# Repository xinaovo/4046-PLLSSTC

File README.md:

# 4046 PLLSSTC

## About this repository

This repository contains PCB designs and documents of the CD4046-based PLLSSTC project.

## PCB Designs

### Power Board

TODO

### 4046 PLL Board

TODO

### Mosfet Driver & GDT Board

TODO

### Full-Bridge Inverter Board

TODO

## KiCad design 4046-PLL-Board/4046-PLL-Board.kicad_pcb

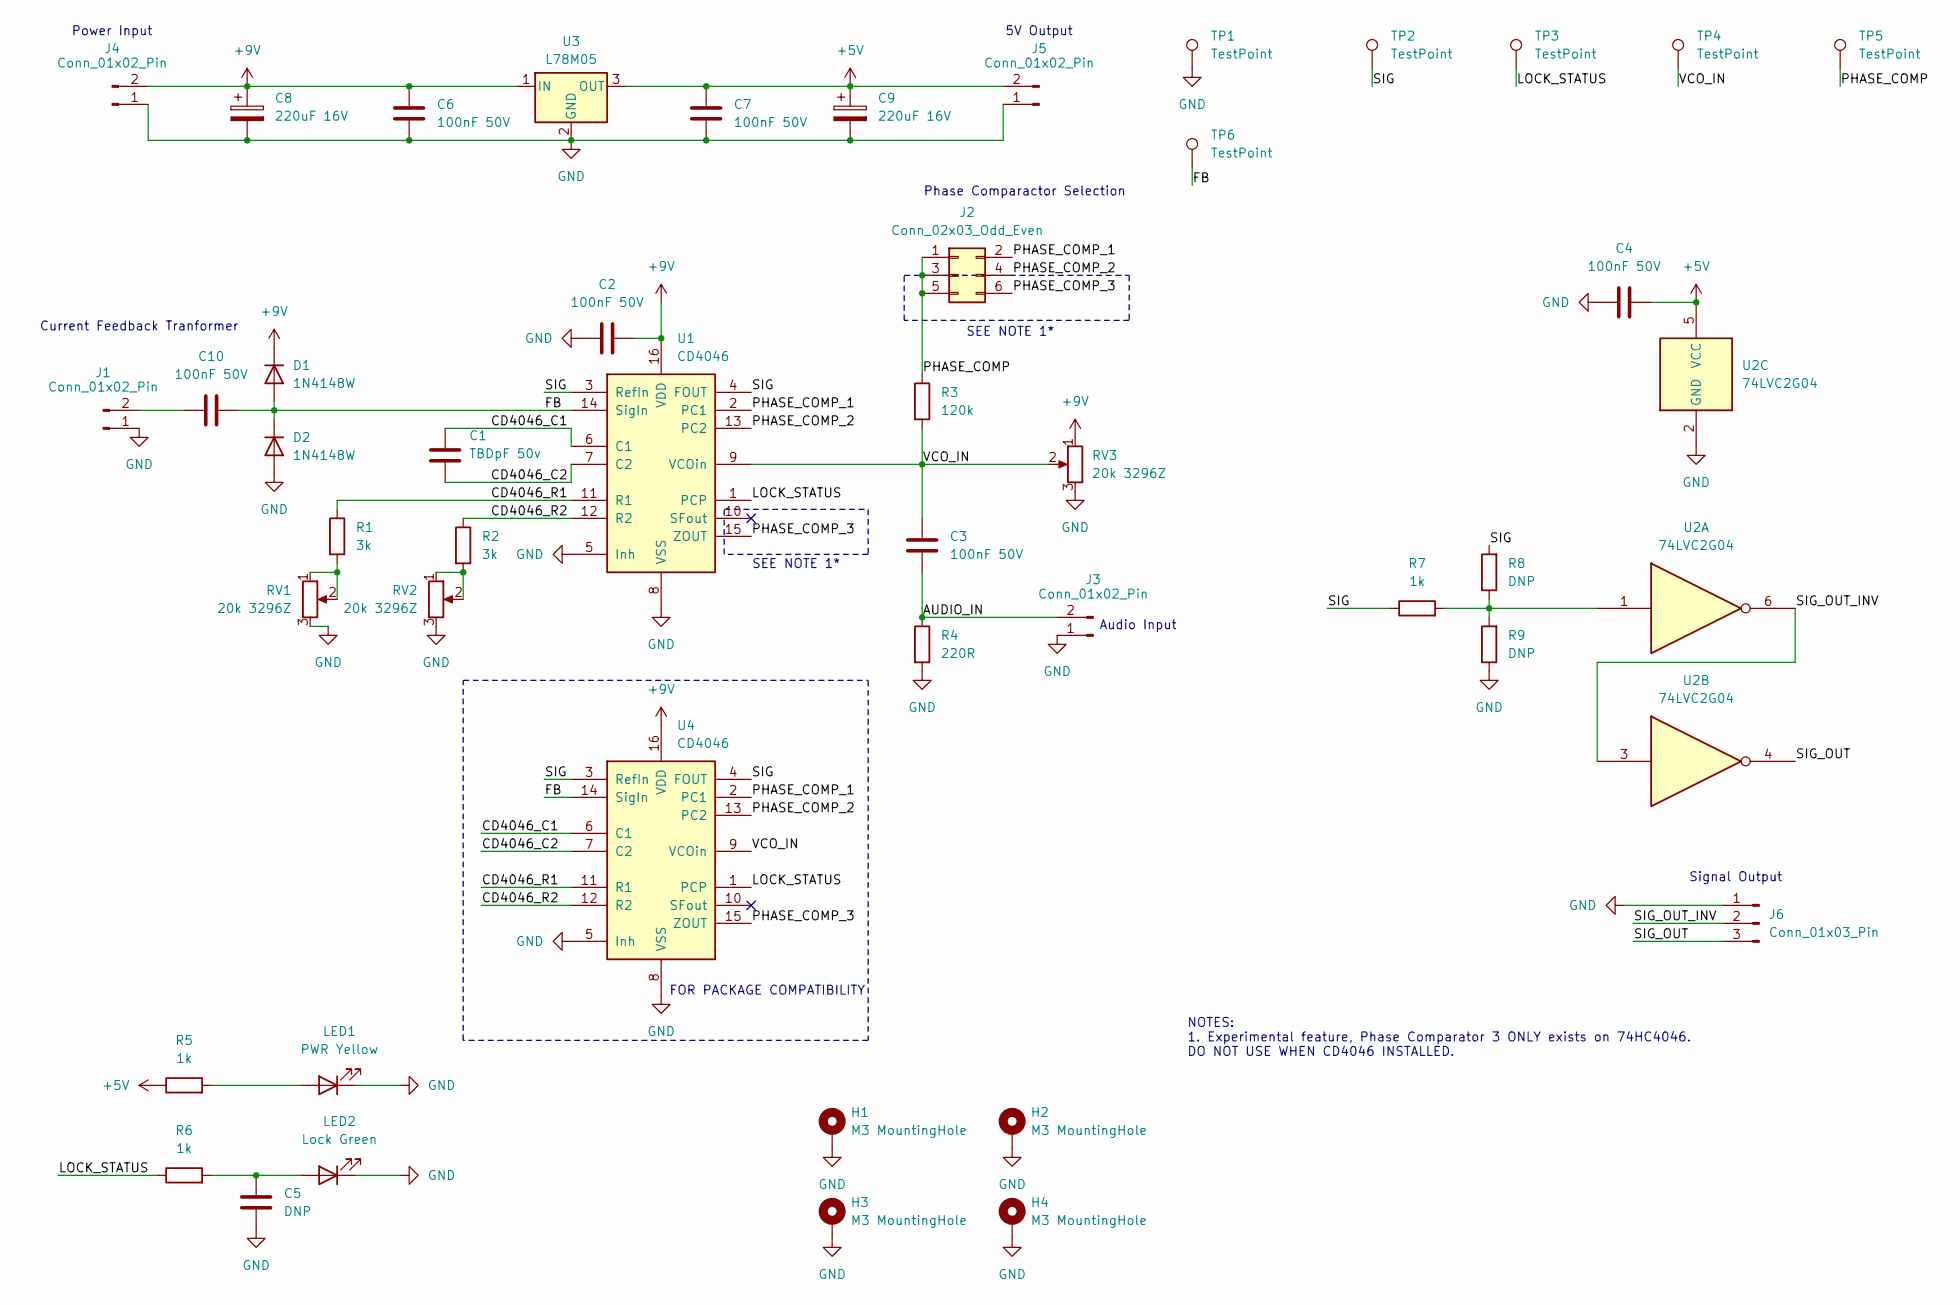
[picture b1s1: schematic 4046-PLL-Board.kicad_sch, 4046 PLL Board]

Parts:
C1: TBDpF 50v; C_Disc_D5.0mm_W2.5mm_P2.50mm
C2, C4, C6, C7: 100nF 50V; C_0603_1608Metric_Pad1.08x0.95mm_HandSolder
C3, C10: 100nF 50V; C_Disc_D5.0mm_W2.5mm_P2.50mm
C5: DNP; C_0603_1608Metric_Pad1.08x0.95mm_HandSolder
C8, C9: 220uF 16V; CP_Radial_D6.3mm_P2.50mm
D1, D2: 1N4148W; D_SOD-123
H1, H2, H3, H4: M3 MountingHole; MountingHole_3.2mm_M3_DIN965_Pad_TopBottom
J1, J3, J4, J5: Conn_01x02_Pin; JST_XH_B2B-XH-A_1x02_P2.50mm_Vertical
J2: Conn_02x03_Odd_Even; PinHeader_2x03_P2.54mm_Vertical
J6: Conn_01x03_Pin; JST_XH_B3B-XH-A_1x03_P2.50mm_Vertical
LED1: PWR Yellow; LED_0603_1608Metric_Pad1.05x0.95mm_HandSolder
LED2: Lock Green; LED_0603_1608Metric_Pad1.05x0.95mm_HandSolder
R1, R2: 3k; R_0603_1608Metric_Pad0.98x0.95mm_HandSolder
R3: 120k; R_Axial_DIN0207_L6.3mm_D2.5mm_P7.62mm_Horizontal
R4: 220R; R_Axial_DIN0207_L6.3mm_D2.5mm_P7.62mm_Horizontal
R5, R6, R7: 1k; R_0603_1608Metric_Pad0.98x0.95mm_HandSolder
R8, R9: DNP; R_0603_1608Metric_Pad0.98x0.95mm_HandSolder
RV1, RV2, RV3: 20k 3296Z; Potentiometer_Bourns_3296X_Horizontal
TP1, TP2, TP3, TP4, TP5, TP6: TestPoint; TestPoint_Loop_D2.50mm_Drill1.0mm
U1: CD4046; SOIC-16_4.55x10.3mm_P1.27mm
U2: 74LVC2G04; SOT-23-6_Handsoldering
U3: L78M05; TO-252-2
U4: CD4046; SOIC-16_3.9x9.9mm_P1.27mm

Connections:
+5V: C4.2, C7.2, C9.1, J5.2, R5.1, U2.5 (VCC), U3.3 (OUT)
+9V: C2.2, C6.2, C8.1, D1.1 (K), J4.2, RV3.1, U1.16 (VDD), U3.1 (IN), U4.16 (VDD)
/AUDIO_IN: C3.1, J3.2, R4.1
/CD4046_C1: C1.1, U1.6 (C1), U4.6 (C1)
/CD4046_C2: C1.2, U1.7 (C2), U4.7 (C2)
/CD4046_R1: R1.1, U1.11 (R1), U4.11 (R1)
/CD4046_R2: R2.1, U1.12 (R2), U4.12 (R2)
/FB: C10.1, D1.2 (A), D2.1 (K), TP6.1, U1.14 (SigIn), U4.14 (SigIn)
/LOCK_STATUS: R6.1, TP3.1, U1.1 (PCP), U4.1 (PCP)
/PHASE_COMP: J2.1, J2.3, J2.5, R3.1, TP5.1
/PHASE_COMP_1: J2.2, U1.2 (PC1), U4.2 (PC1)
/PHASE_COMP_2: J2.4, U1.13 (PC2), U4.13 (PC2)
/PHASE_COMP_3: J2.6, U1.15 (ZOUT), U4.15 (ZOUT)
/SIG: R7.1, R8.2, TP2.1, U1.3 (RefIn), U1.4 (FOUT), U4.3 (RefIn), U4.4 (FOUT)
/SIG_OUT: J6.3, U2.4
/SIG_OUT_INV: J6.2, U2.3, U2.6
/VCO_IN: C3.2, R3.2, RV3.2, TP4.1, U1.9 (VCOin), U4.9 (VCOin)
GND: C2.1, C4.1, C5.1, C6.1, C7.1, C8.2, C9.2, D2.2 (A), H1.1, H2.1, H3.1, H4.1, J1.1, J3.1, J4.1, J5.1, J6.1, LED1.1 (K), LED2.1 (K), R4.2, R9.1, RV1.3, RV2.3, RV3.3, TP1.1, U1.5 (Inh), U1.8 (VSS), U2.2 (GND), U3.2 (GND), U4.5 (Inh), U4.8 (VSS)
unnamed: C10.2, J1.2
unnamed: LED1.2 (A), R5.2
unnamed: C5.2, LED2.2 (A), R6.2
unnamed: R1.2, RV1.1, RV1.2
unnamed: R2.2, RV2.1, RV2.2
unnamed: R7.2, R8.1, R9.2, U2.1

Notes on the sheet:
Audio Input
SEE NOTE 1*
Signal Output
Current Feedback Tranformer
Power Input
Phase Comparactor Selection
5V Output
FOR PACKAGE COMPATIBILITY
NOTES: 1. Experimental feature, Phase Comparator 3 ONLY exists on 74HC4046. DO NOT USE WHEN CD4046 INSTALLED.

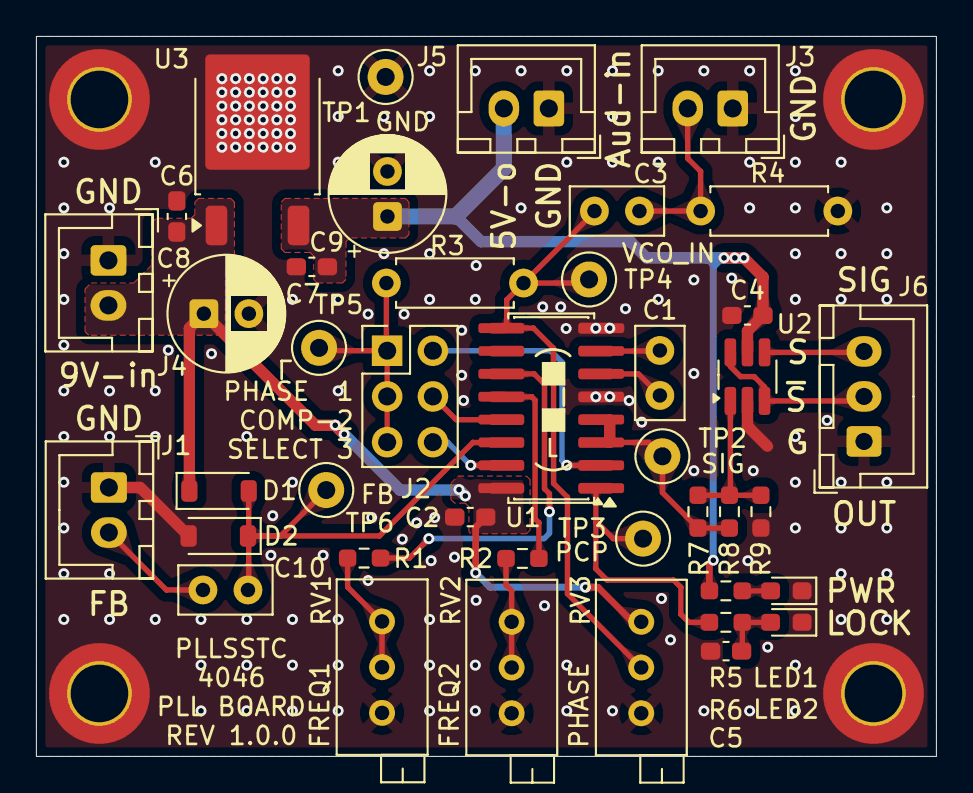
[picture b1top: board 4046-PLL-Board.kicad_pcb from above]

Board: 2 copper layers, 50.0 x 40.0 mm, 46 parts (0 on the bottom side), 24 nets.

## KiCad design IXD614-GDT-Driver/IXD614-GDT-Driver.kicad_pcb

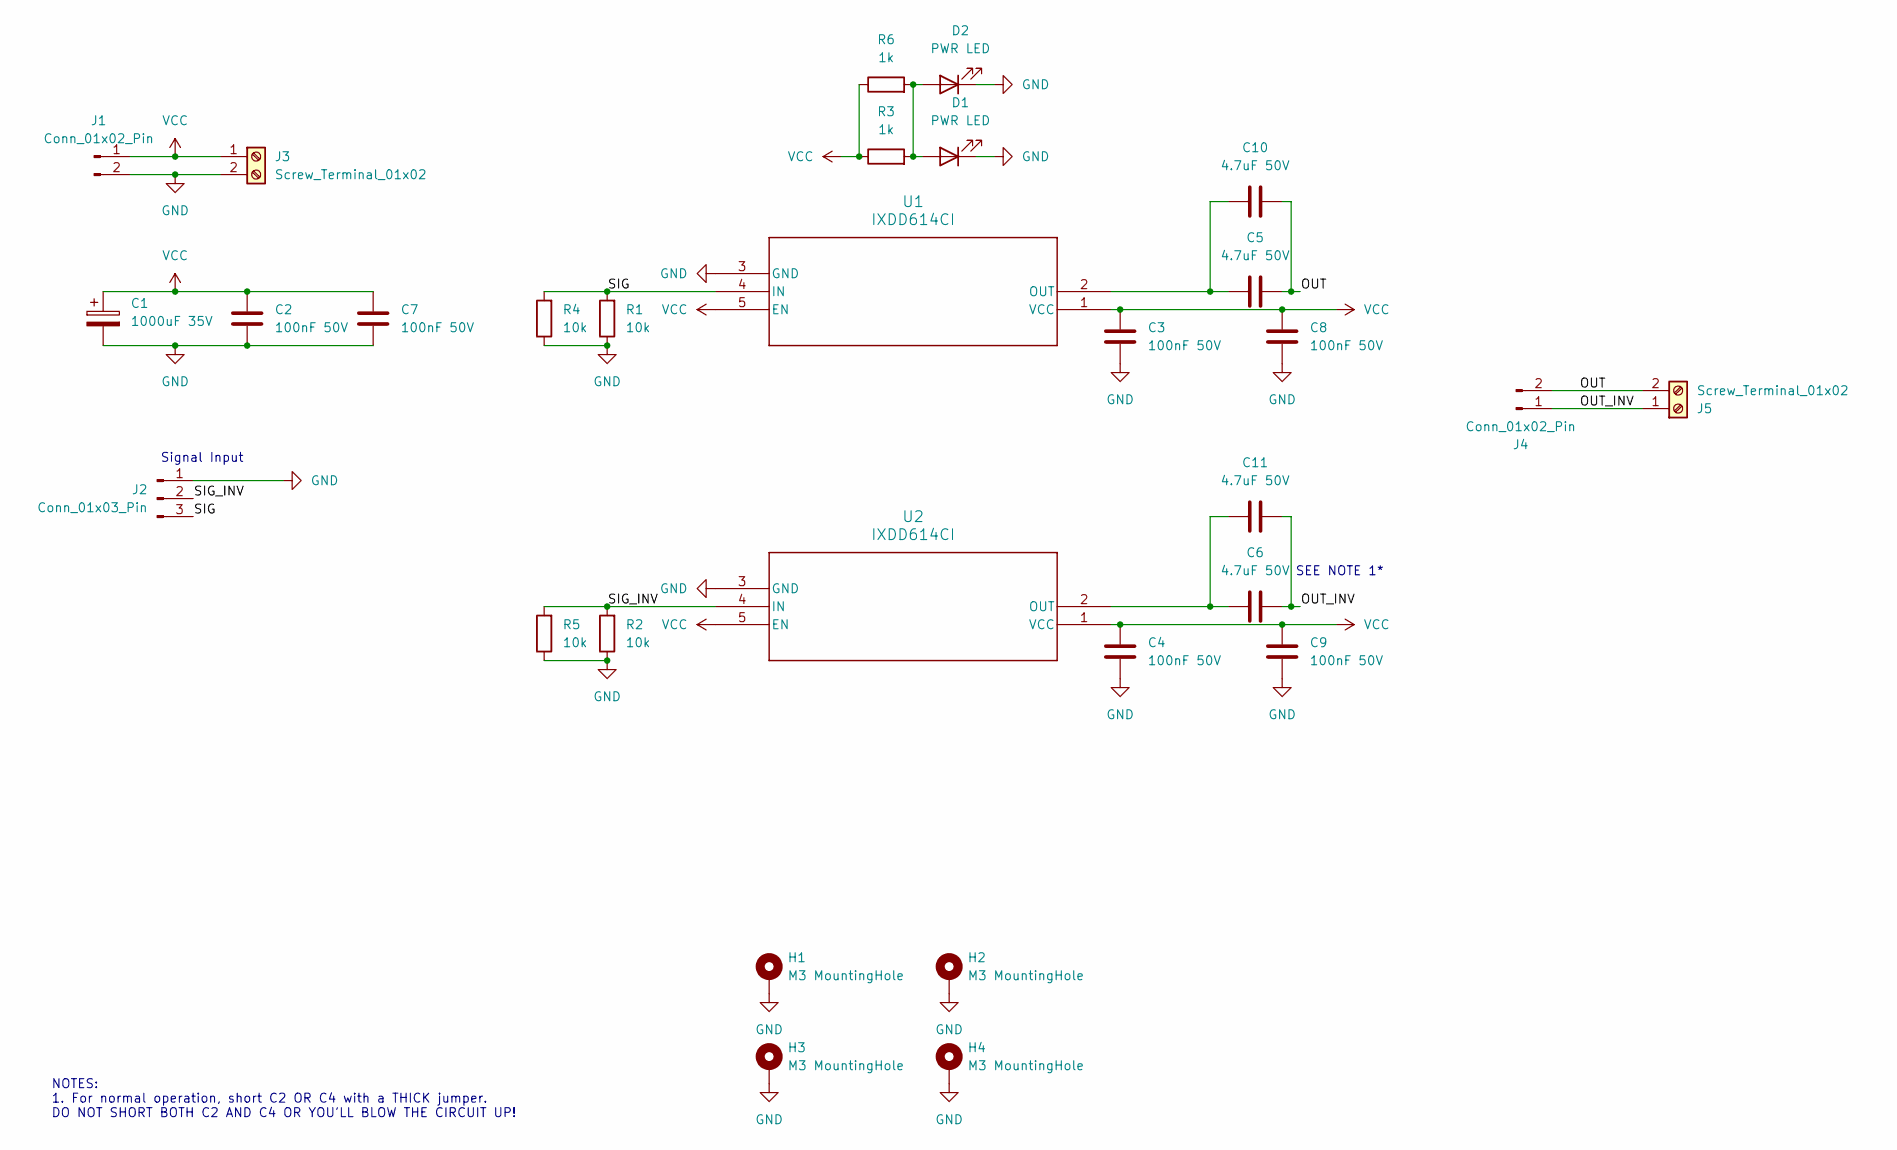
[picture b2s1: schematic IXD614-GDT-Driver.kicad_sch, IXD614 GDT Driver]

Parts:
C1: 1000uF 35V; CP_Radial_D10.0mm_P2.50mm_P5.00mm
C2, C3, C4: 100nF 50V; C_Disc_D5.0mm_W2.5mm_P5.00mm
C5, C6: 4.7uF 50V; C_Disc_D6.0mm_W4.4mm_P5.00mm
C7, C8, C9: 100nF 50V; C_0603_1608Metric_Pad1.08x0.95mm_HandSolder
C10, C11: 4.7uF 50V; C_1210_3225Metric
D1: PWR LED; LED_D5.0mm
D2: PWR LED; LED_0603_1608Metric_Pad1.05x0.95mm_HandSolder
H1, H2, H3, H4: M3 MountingHole; MountingHole_3.2mm_M3_DIN965_Pad_TopBottom
J1, J4: Conn_01x02_Pin; JST_XH_B2B-XH-A_1x02_P2.50mm_Vertical
J2: Conn_01x03_Pin; JST_XH_B3B-XH-A_1x03_P2.50mm_Vertical
J3, J5: Screw_Terminal_01x02; Wuerth_691311400102_P7.62mm
R1, R2: 10k; R_Axial_DIN0207_L6.3mm_D2.5mm_P7.62mm_Horizontal
R3: 1k; R_Axial_DIN0207_L6.3mm_D2.5mm_P7.62mm_Horizontal
R4, R5: 10k; R_0603_1608Metric_Pad0.98x0.95mm_HandSolder
R6: 1k; R_0603_1608Metric_Pad0.98x0.95mm_HandSolder
U1, U2: IXDD614CI; TO-220-5_Vertical

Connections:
/OUT: C5.2, C10.2, J4.2, J5.2
/OUT_INV: C6.2, C11.2, J4.1, J5.1
/SIG: J2.3, R1.2, R4.2, U1.4 (IN)
/SIG_INV: J2.2, R2.2, R5.2, U2.4 (IN)
GND: C1.2, C2.2, C3.2, C4.2, C7.2, C8.2, C9.2, D1.1 (K), D2.1 (K), H1.1, H2.1, H3.1, H4.1, J1.2, J2.1, J3.2, R1.1, R2.1, R4.1, R5.1, U1.3 (GND), U2.3 (GND)
unnamed: D1.2 (A), D2.2 (A), R3.2, R6.2
unnamed: C5.1, C10.1, U1.2 (OUT)
unnamed: C6.1, C11.1, U2.2 (OUT)
VCC: C1.1, C2.1, C3.1, C4.1, C7.1, C8.1, C9.1, J1.1, J3.1, R3.1, R6.1, U1.1 (VCC), U1.5 (EN), U2.1 (VCC), U2.5 (EN)

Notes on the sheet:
SEE NOTE 1*
Signal Input
NOTES: 1. For normal operation, short C2 OR C4 with a THICK jumper. DO NOT SHORT BOTH C2 AND C4 OR YOU'LL BLOW THE CIRCUIT UP!

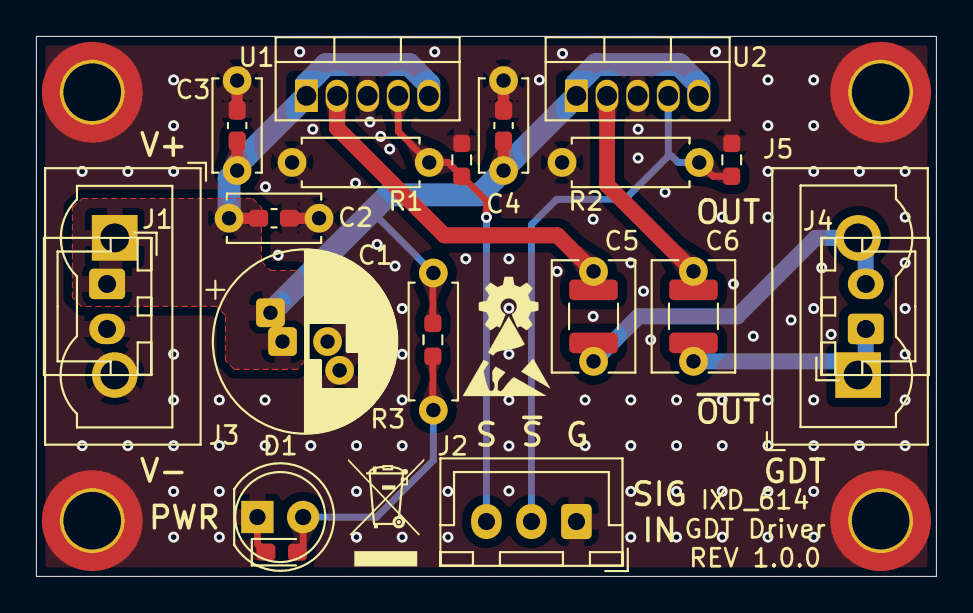
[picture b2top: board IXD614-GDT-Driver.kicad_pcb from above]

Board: 2 copper layers, 50.0 x 30.0 mm, 30 parts (0 on the bottom side), 9 nets.

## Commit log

2025-10-28 add .gitignore
2025-10-28 add 4046 PLL Board design REV 1.0.0
2025-10-28 add MOSFET Driver design files and author info
2025-11-17 add IXD614 GDT Driver design REV 1.0.0
2025-11-18 add support for CD4046 in SO-16-208mil package on PLL board
2025-11-18 modified stitching vias
